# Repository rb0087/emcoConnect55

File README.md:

# emcoConnect55
Design for circuit board and system connections to connect Emco PCMill 55 to an Ethernet Smoothstepper

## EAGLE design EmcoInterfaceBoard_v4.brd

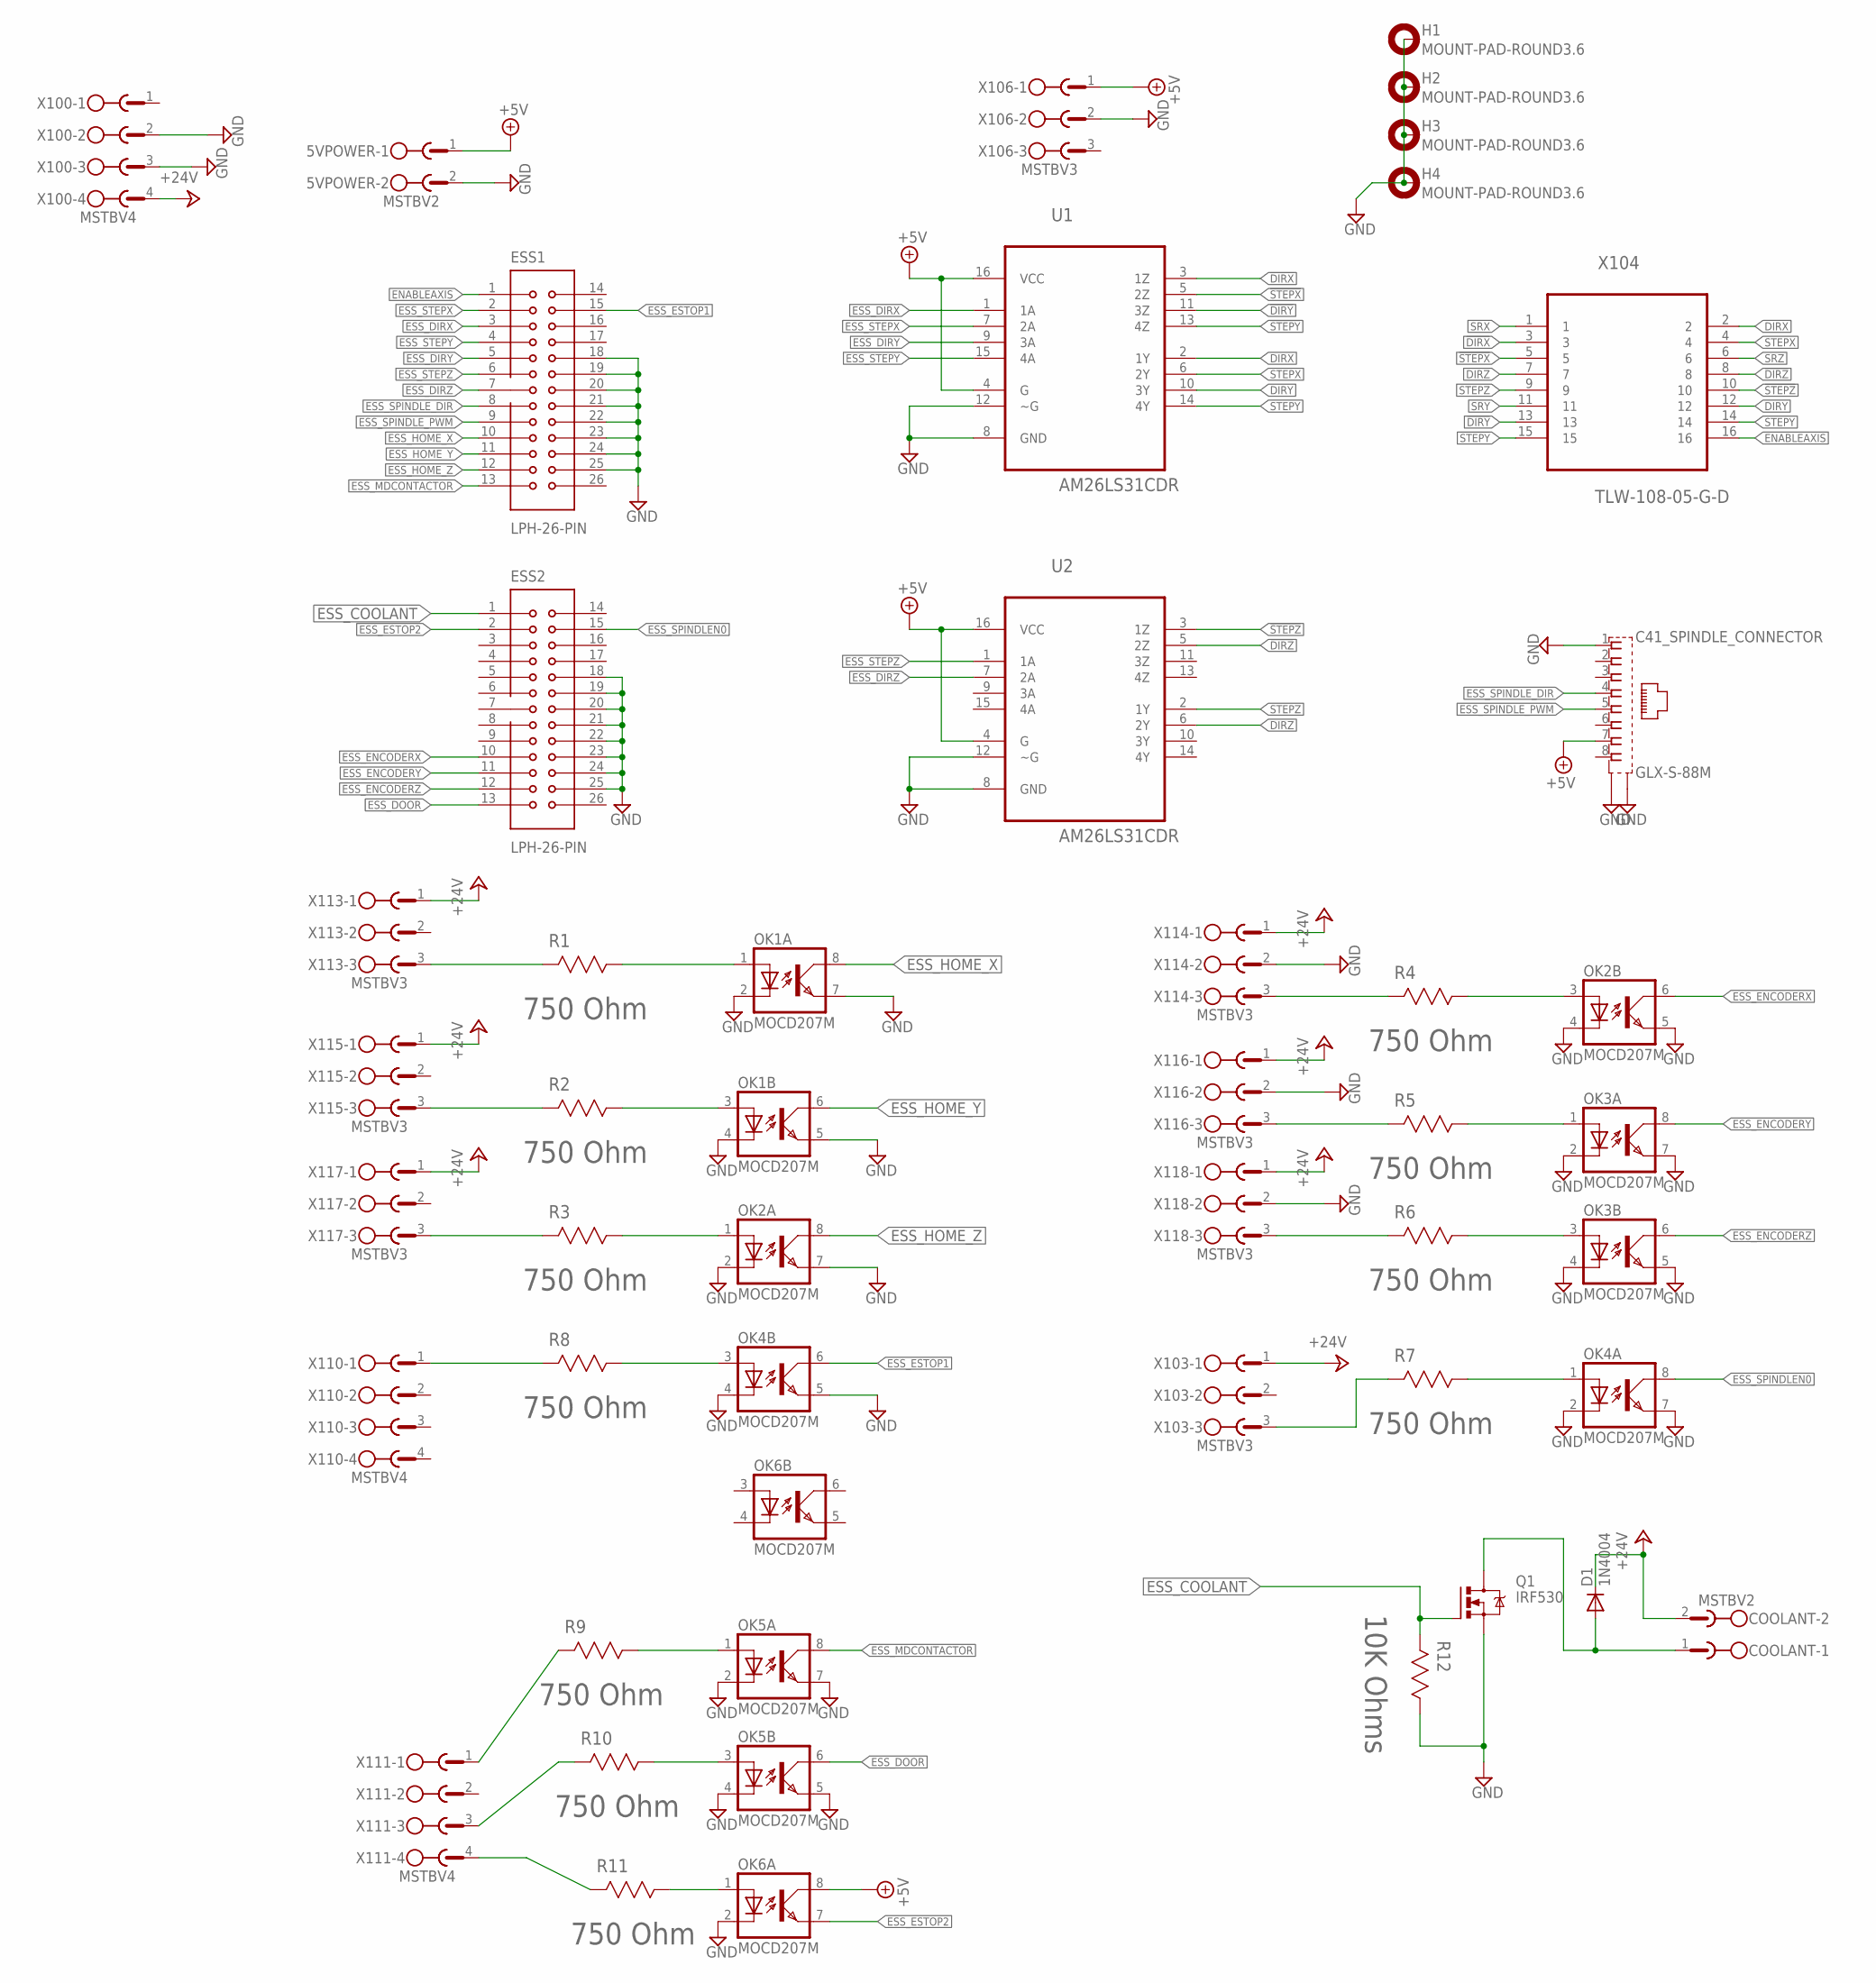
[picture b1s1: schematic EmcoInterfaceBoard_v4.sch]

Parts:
5VPOWER: MSTBV2; MPN 1521860000
C41_SPINDLE_CONNECTOR: GLX-S-88M; MPN 43860-0025
COOLANT: MSTBV2; MPN 1521860000
D1: 1N4004; DO41-10; MPN 1N4007.
ESS1, ESS2: LPH-26-PIN; LOWPROFILEHEADER-26PIN; MPN 5103308-6
H1, H2, H3, H4: MOUNT-PAD-ROUND3.6; 3,6-PAD
OK1, OK2, OK3, OK4, OK5, OK6: MOCD207M; SOIC08-FAIRCHILD; MPN MOCD207M
Q1: IRF530; TO220BV; MPN FQP30N06L
R1, R2, R3, R4, R5, R6, R7, R8, R9, R10, R11: 750 Ohm; RESC6332X71N
R12: 10K Ohms; RESC3216X71N; MPN RC1206FR-0710KL
U1, U2: AM26LS31CDR; SOIC127P600X175-16N
X100, X110, X111: MSTBV4; MPN 1522060000
X103, X106, X113, X114, X115, X116, X117, X118: MSTBV3; MPN 1521960000
X104: TLW-108-05-G-D; SAMTEC_TLW-108-05-G-D; MPN 2-1761603-6

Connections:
!DIRX!: U1.3 (1Z), X104.3
!DIRY!: U1.11 (3Z), X104.13
!DIRZ!: U2.5 (2Z), X104.8
!STEPX!: U1.5 (2Z), X104.5
!STEPY!: U1.13 (4Z), X104.15
!STEPZ!: U2.3 (1Z), X104.10
+5V: 5VPOWER.1, C41_SPINDLE_CONNECTOR.7, OK6.8 (COL), U1.4 (G), U1.16 (VCC), U2.4 (G), U2.16 (VCC), X106.1
+24V: COOLANT.2, D1.C, X100.4, X103.1, X113.1, X114.1, X115.1, X116.1, X117.1, X118.1
DIRX: U1.2 (1Y), X104.2
DIRY: U1.10 (3Y), X104.12
DIRZ: U2.6 (2Y), X104.7
ENABLEAXIS: ESS1.1, X104.16
ENCODERX: R4.2, X114.3
ENCODERY: R5.2, X116.3
ENCODERZ: R6.2, X118.3
ESS_COOLANT: ESS2.1, Q1.G, R12.2 (R2)
ESS_DIRX: ESS1.3, U1.1 (1A)
ESS_DIRY: ESS1.5, U1.9 (3A)
ESS_DIRZ: ESS1.7, U2.7 (2A)
ESS_DOOR: ESS2.13, OK5.6 (COL)
ESS_ENCODERX: ESS2.10, OK2.6 (COL)
ESS_ENCODERY: ESS2.11, OK3.8 (COL)
ESS_ENCODERZ: ESS2.12, OK3.6 (COL)
ESS_ESTOP1: ESS1.15, OK4.6 (COL)
ESS_ESTOP2: ESS2.2, OK6.7 (EMIT)
ESS_HOME_X: ESS1.10, OK1.8 (COL)
ESS_HOME_Y: ESS1.11, OK1.6 (COL)
ESS_HOME_Z: ESS1.12, OK2.8 (COL)
ESS_MDCONTACTOR: ESS1.13, OK5.8 (COL)
ESS_SPINDLEN0: ESS2.15, OK4.8 (COL)
ESS_SPINDLE_DIR: C41_SPINDLE_CONNECTOR.4, ESS1.8
ESS_SPINDLE_PWM: C41_SPINDLE_CONNECTOR.5, ESS1.9
ESS_STEPX: ESS1.2, U1.7 (2A)
ESS_STEPY: ESS1.4, U1.15 (4A)
ESS_STEPZ: ESS1.6, U2.1 (1A)
GND: 5VPOWER.2, C41_SPINDLE_CONNECTOR.1, C41_SPINDLE_CONNECTOR.S1, C41_SPINDLE_CONNECTOR.S2, ESS1.18, ESS1.19, ESS1.20, ESS1.21, ESS1.22, ESS1.23, ESS1.24, ESS1.25, ESS2.18, ESS2.19, ESS2.20, ESS2.21, ESS2.22, ESS2.23, ESS2.24, ESS2.25, H1.B3,6, H2.B3,6, H3.B3,6, H4.B3,6, OK1.2 (C), OK1.4 (C), OK1.5 (EMIT), OK1.7 (EMIT), OK2.2 (C), OK2.4 (C), OK2.5 (EMIT), OK2.7 (EMIT), OK3.2 (C), OK3.4 (C), OK3.5 (EMIT), OK3.7 (EMIT), OK4.2 (C), OK4.4 (C), OK4.5 (EMIT), OK4.7 (EMIT), OK5.2 (C), OK5.4 (C), OK5.5 (EMIT), OK5.7 (EMIT), OK6.2 (C), Q1.S, R12.1 (R1), U1.8 (GND), U1.12 (~G), U2.8 (GND), U2.12 (~G), X100.2, X100.3, X106.2, X114.2, X116.2, X118.2
unnamed: OK3.3 (A), R6.1
unnamed: OK3.1 (A), R5.1
unnamed: OK2.3 (A), R4.1
unnamed: OK1.3 (A), R2.1
unnamed: OK2.1 (A), R3.1
unnamed: OK1.1 (A), R1.1
unnamed: OK4.1 (A), R7.1
unnamed: R1.2, X113.3
unnamed: R7.2, X103.3
unnamed: R2.2, X115.3
unnamed: R8.2, X110.1
unnamed: R3.2, X117.3
unnamed: OK4.3 (A), R8.1
unnamed: R9.2, X111.1
unnamed: OK5.1 (A), R9.1
unnamed: OK5.3 (A), R10.1
unnamed: R10.2, X111.3
unnamed: OK6.1 (A), R11.1
unnamed: R11.2, X111.4
unnamed: COOLANT.1, D1.A, Q1.D
SRX: X104.1
SRY: X104.11
SRZ: X104.6
STEPX: U1.6 (2Y), X104.4
STEPY: U1.14 (4Y), X104.14
STEPZ: U2.2 (1Y), X104.9

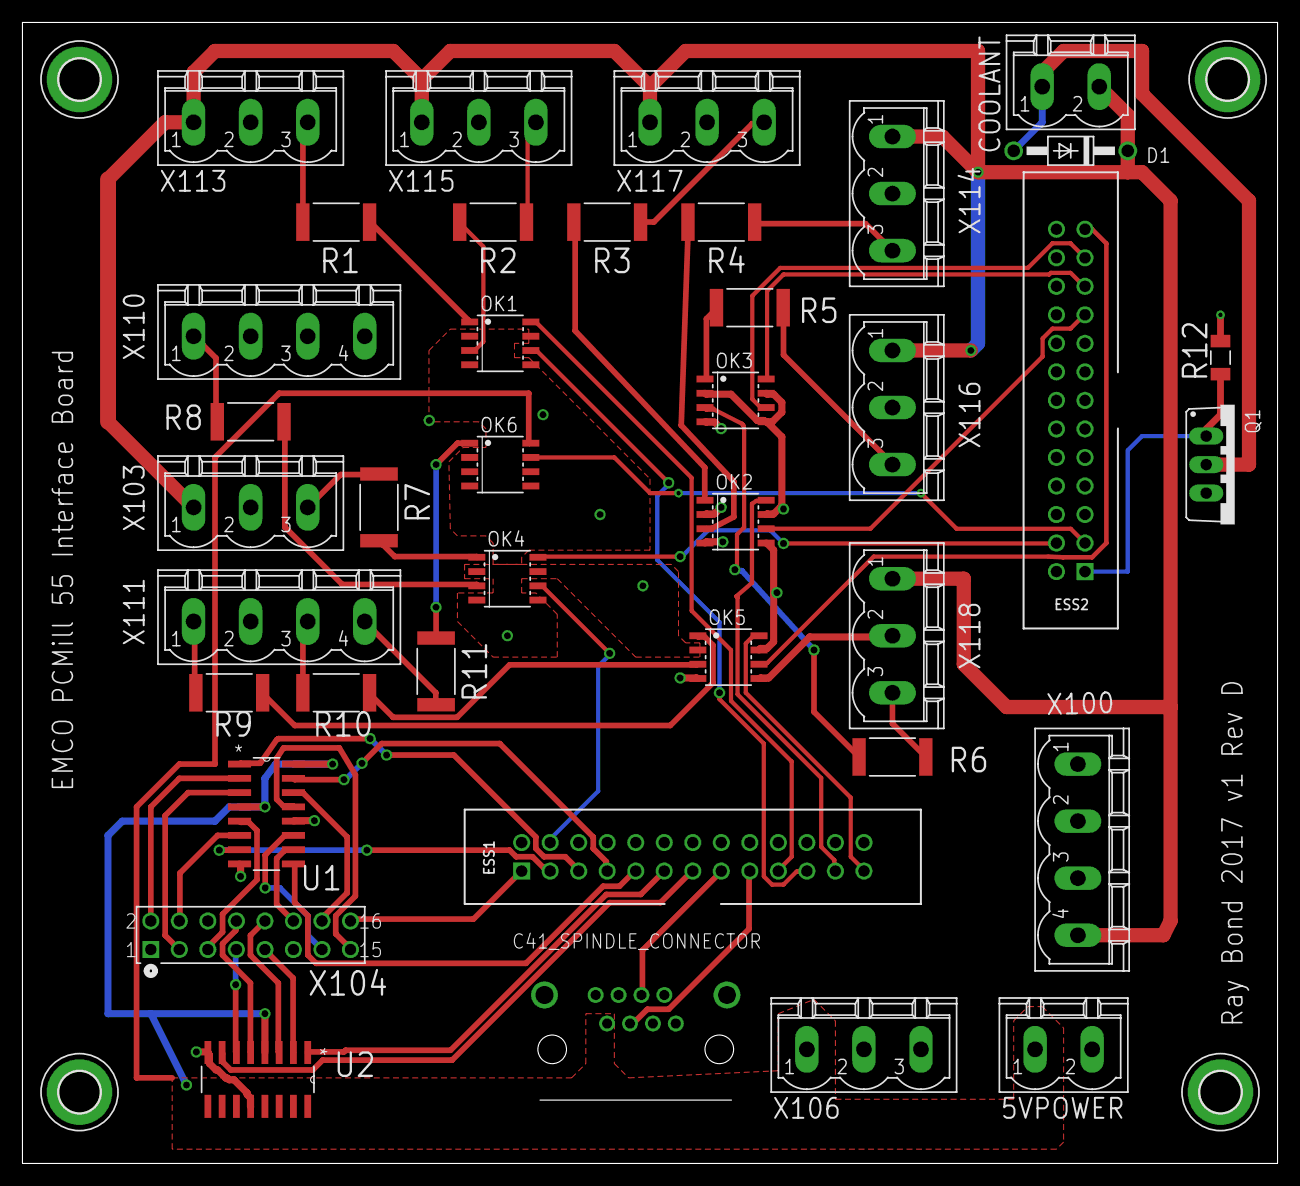
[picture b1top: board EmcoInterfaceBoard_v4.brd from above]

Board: 2 copper layers, 111.8 x 101.6 mm, 43 parts (0 on the bottom side), 59 nets.

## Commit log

2017-03-12 Added Gerber files and LTSpice simulation files
2017-03-18 Create FIXME
